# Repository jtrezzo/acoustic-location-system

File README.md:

acoustic-location-system
========================

Software and hardware designs for an acoustic location system suitable for small underwater ROVs such as OpenROV

This project is about developing an acoustic based location system for small ROVs.

Much of the early work that we have been doing is in the blog: https://forum.openrov.com/t/acoustic-modems-location-and-pingers
That blog covers broader topics, so I wanted to start a forum discussion specifically for developing the acoustic location system.  https://forum.openrov.com/t/acoustic-location-system

Knowing where you are when exploring and gathering images and data is clearly a vital piece of information.  GPS systems provide this on land.  Underwater, radio waves that GPS depends on to function are absorbed by water.  Acoustic signals are one of the best alternatives to transmit information for location and other data communication.  Commercial underwater modem systems exist today and are widely used in exploration, but suitable systems for low-cost small size platforms like OpenROV are not available.  This project plans to deliver such a system and is in-part inspired by university research in this area – Bridget Benson’s UCSD PhD Thesis http://haduken.ucsd.edu/papers/phd-thesis-benson.pdf is one example.
Information about 3D location in real-time is a key enabler for many scientific and exploratory needs. The technology to do this is known, but has not been scaled down for systems of this size. With location information, one could map any discoveries (sunken ships, archeological sites, and coral reefs are some examples). Maps of the ocean/lake/cave can be made with location and sensor information together. Virtual Reality and 3D gaming technology could be used to represent information about an exploration either in real-time (shared over the internet) or archived for many to explore on-line as they study results of explorations.
The technical approach is to use acoustic transmissions (ultrasonic sonar) from known locations on the surface (GPS would be used to maintain location of the sender). The ROV would have a receiver unit on board and can determine the time for the signal to arrive. That information along with depth, temperature and the on-board IMU (gyro, compass, accelerometers) would be used to determine/compute location. Location information would be available to the operator of the ROV and a graphical display could be developed (possibly in conjunction with maps of the bottom if available) to help with navigation.

Current status and near term work items:
Working designs for ultrasonic Power AMP and receiver exist and initial testing with 40KHz piezoelectric transducers has begun.  A micro-controller or processor can be used to generate a 40KHz square wave pulse which is shaped and amplified into a sine wave to drive the transducer.  Currently the amplifier produces a 27Vp-p signal.  If testing shows that this is not enough to generate a powerful enough ultrasonic pulse, a step-up transformer may be required.
The high gain (> 100), high input impedance (FET front end) receiver amplifier design includes a narrow band pass filter to allow only frequencies in the desired range to be amplified.  This receiver needs to be packaged and integrated with the ROV electronics along with a micro-controller to process the waveform (>100 samples/sec and real-time FFT processing required).  
System level: Some how the timing for the start of the pulse from each transmitter (correlated with GPS location at time of transmission) must be matched against the time the first pulse is received (any delayed echoes would be rejected).  The time of travel for the pulse would be used to calculate the distance from the transmitter (with know location) and along with depth information, water temperature, salinity (salt or fresh) and IMU data (plus and location history - dead reckoning, etc.) location would be determined. Data from a second transmitter some distance from the first would greatly help the calculation (see Virtual Long Baseline VLBL Navigation).  The transmissions and calculations should be able to be done every tenth of a second to provide timely location.
I will establish a location on GitHub for this project and start to organize existing material there.  for now, take a look at the blog https://forum.openrov.com/t/acoustic-modems-location-and-pingers.
It would speed things up if I got some help with the micro-controller software while I continue with the electronics and in the water testing.  To do: sample the signal and determine when a 40KHz pulse arrives.  Digital signal processing (DSP) analysis would be the likely approach.  Also will need to determine which micro-controller is adequate to handle this processing load.  I will collect some raw data samples using my NI VirtualBench if someone just wants to work on the DSP part.
There are a few folks already interested, and some possibility of collaboration is there.
If you are interested in getting involved, please let me know and what area(s) you think you can hep with.

I have added a folder with results from acoustic testing.  It includes the results of some initial DSP processing using MATLAB, courtesy of Frikk Solberg of Norway.

Regards,

Jim Trezzo
jtrezzo@trezco.com

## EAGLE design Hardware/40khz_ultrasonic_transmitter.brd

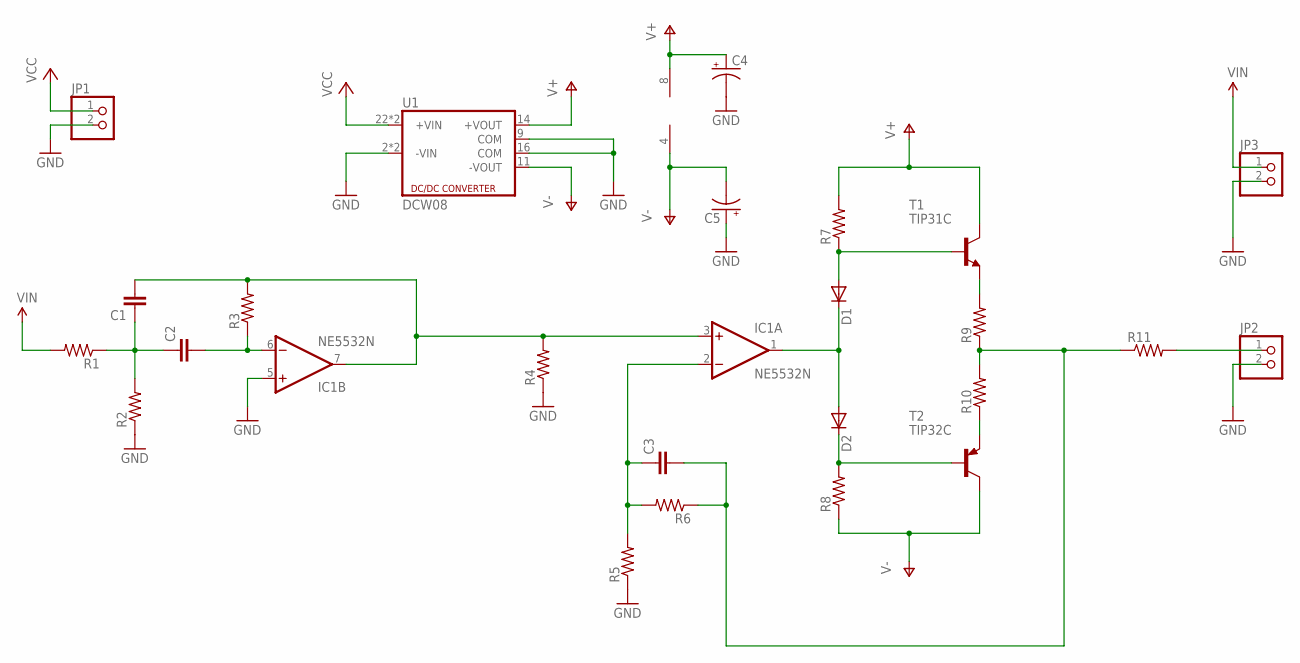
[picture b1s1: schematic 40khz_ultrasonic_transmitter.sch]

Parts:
C1, C2, C3: CAPPTH2; CAP-PTH-SMALL2
C4, C5: CAP_POLPTH1; CPOL-RADIAL-100UF-25V
D1, D2: DIODE1N4148; DIODE-1N4148
IC1: NE5532N; DIL08
JP1, JP2, JP3: PINHD-1X2; 1X02
R1, R2, R3, R4, R5, R6, R7, R8, R9, R10: RESISTORPTH-1/4W; AXIAL-0.4
R11: RESISTORPTH-2W; AXIAL-0.8
T1: TIP31C; TO220
T2: TIP32C; TO220
U1: DCW08

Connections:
GND: C4.2 (-), C5.1 (+), IC1.5 (+IN), JP1.2, JP2.2, JP3.2, R2.P$1 (1), R4.P$1 (1), R5.P$1 (1), U1.2 (-VIN), U1.3 (-VIN), U1.9 (COM), U1.16 (COM)
unnamed: C3.2, R6.P$1 (1), R9.P$1 (1), R10.P$2 (2), R11.P$1 (1)
unnamed: R9.P$2 (2), T1.3 (E)
unnamed: R10.P$1 (1), T2.3 (E)
unnamed: D1.A, R7.P$1 (1), T1.1 (B)
unnamed: D2.C, R8.P$2 (2), T2.1 (B)
unnamed: C1.2, IC1.3 (+IN), IC1.7 (OUT), R3.P$2 (2), R4.P$2 (2)
unnamed: C1.1, C2.1, R1.P$1 (1), R2.P$2 (2)
unnamed: C3.1, IC1.2 (-IN), R5.P$2 (2), R6.P$2 (2)
unnamed: C2.2, IC1.6 (-IN), R3.P$1 (1)
unnamed: JP2.1, R11.P$2 (2)
unnamed: D1.C, D2.A, IC1.1 (OUT)
V+: C4.1 (+), IC1.8 (V+), R7.P$2 (2), T1.2 (C), U1.14 (+VOUT)
V-: C5.2 (-), IC1.4 (V-), R8.P$1 (1), T2.2 (C), U1.11 (-VOUT)
VCC: JP1.1, U1.22 (+VIN), U1.23 (+VIN)
VIN: JP3.1, R1.P$2 (2)

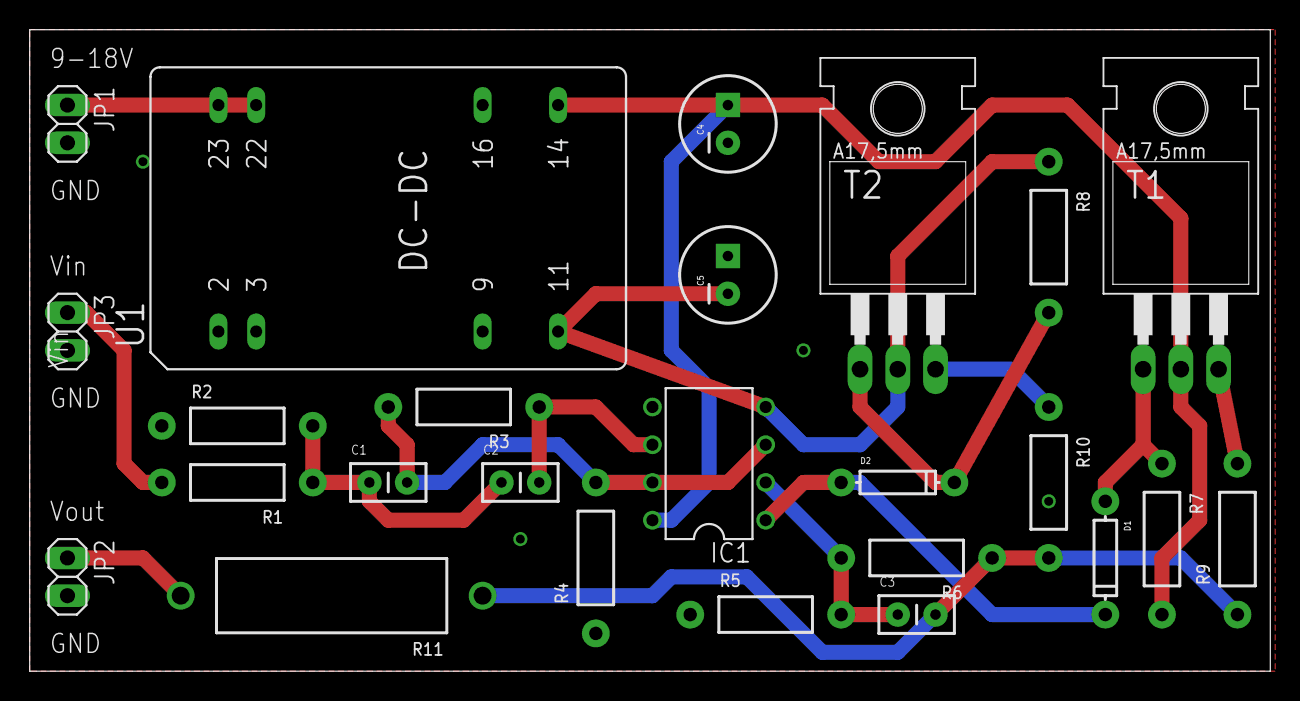
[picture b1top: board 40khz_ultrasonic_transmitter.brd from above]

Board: 2 copper layers, 83.5 x 43.2 mm, 25 parts (0 on the bottom side), 16 nets.

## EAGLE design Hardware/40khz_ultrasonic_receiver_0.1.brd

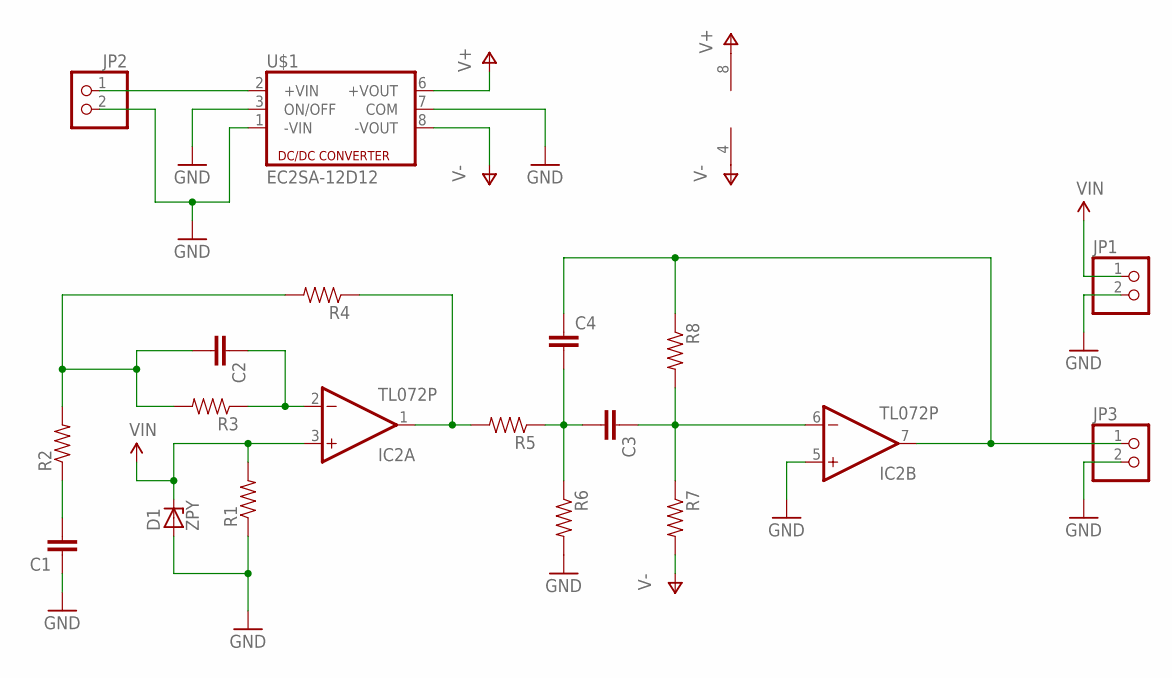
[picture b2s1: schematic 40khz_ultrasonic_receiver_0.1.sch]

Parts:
C1, C2, C3, C4: CAPPTH; CAP-PTH-SMALL
D1: ZPY; DO41Z10
IC2: TL072P; DIL08
JP1, JP2, JP3: PINHD-1X2; 1X02
R1, R2, R3, R4, R5, R6, R7, R8: RESISTORPTH-1/4W; AXIAL-0.4
U$1: EC2SA-12D12; EC2SA

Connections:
GND: C1.1, D1.A, IC2.5 (+IN), JP1.2, JP2.2, JP3.2, R1.P$1 (1), R6.P$2 (2), U$1.1 (-VIN), U$1.3 (ON/OFF), U$1.7 (COM)
unnamed: IC2.1 (OUT), R4.P$1 (1), R5.P$2 (2)
unnamed: C3.2, C4.2, R5.P$1 (1), R6.P$1 (1)
unnamed: C2.1, IC2.2 (-IN), R3.P$1 (1)
unnamed: C4.1, IC2.7 (OUT), JP3.1, R8.P$1 (1)
unnamed: C2.2, R2.P$2 (2), R3.P$2 (2), R4.P$2 (2)
unnamed: C3.1, IC2.6 (-IN), R7.P$1 (1), R8.P$2 (2)
unnamed: C1.2, R2.P$1 (1)
unnamed: JP2.1, U$1.2 (+VIN)
V+: IC2.8 (V+), U$1.6 (+VOUT)
V-: IC2.4 (V-), R7.P$2 (2), U$1.8 (-VOUT)
VIN: D1.C, IC2.3 (+IN), JP1.1, R1.P$2 (2)

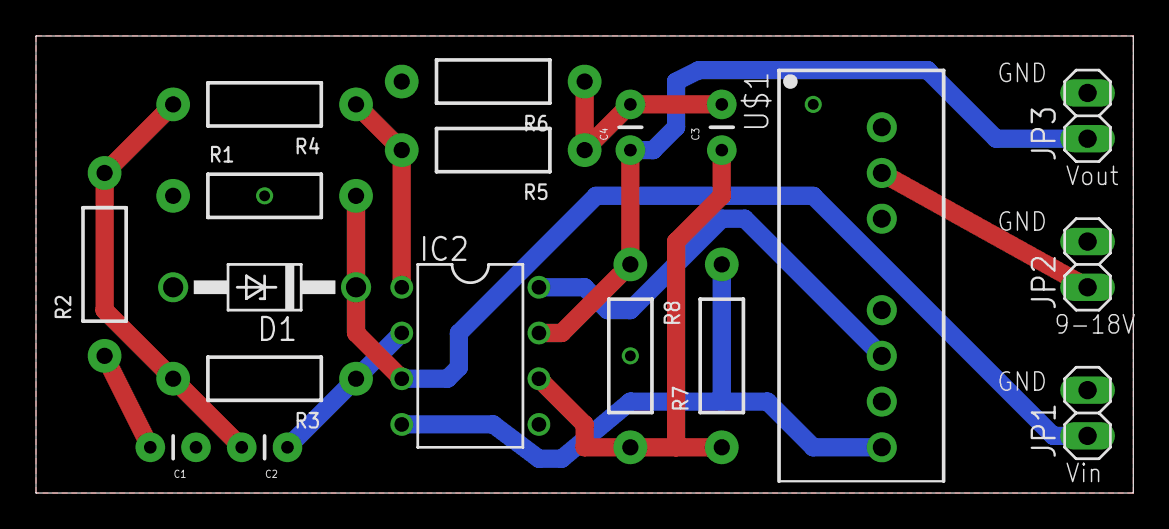
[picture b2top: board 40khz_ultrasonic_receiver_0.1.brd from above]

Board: 2 copper layers, 61.0 x 25.4 mm, 18 parts (0 on the bottom side), 12 nets.

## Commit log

2014-12-01 adding acoustic test data
2014-12-01 Added initial DSP analysis of test data
2015-01-03 Added software folder with data acquisition sw
    Folder contains experimental software for data acquisition and signal
    processing
2015-01-03 add PDF version of software doc
2015-04-16 DSP Python programs for peak detection
2015-06-22 Added dsp_analysis with filter evaluation
2015-06-23 Changed method to plot freq response to freqz instead of chirp
2015-06-23 removed extra lines
2015-08-13 added updated version of adcspeedtest (v3.3) and new TimerPulse program
    adcspeedtest3.3 was rewritten to use a hardware timer interrupt to
    control the sampling rate better. Runs on the teensy 3.1 micro
    controller.
    TimerPulse is a new version of the arduino pulse signal generator.
    This replaces TonePulse and uses timer interrupts for more direct
    control than Tone() allowed.
2015-10-08 Created Rev 0.1 and fixed op-amp wiring
2015-10-08 Added PCB files
2017-04-26 Create folder for OpenROV Sensor Plugin
    Create folder for development work on plugin to allow acoustic sensor
    system (based on micro controller sub-system) to inter-operate with
    OpenROV Node JS based plug-in components
2017-04-26 added text file describing plug-in approach
2017-04-26 Added analog sensor plug-in code
    Added folder “analog sensor” with latest under-development code

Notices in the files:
parts and their libraries:
SparkFun-Passives: Licensing: CC v3.0 Share-Alike You are welcome to use this library for commercial purposes.
